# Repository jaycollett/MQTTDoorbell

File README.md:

# MQTTDoorbell

This repo contains all the project artifacts for my MQTT "smartifier" doorbell module. The module detects a push of the wired doorbell button and triggers a relay to ring the doorbell, the ESP8266 detects this as well and sends a MQTT message to let my HASS.IO server know. From there I trigger automated notifications as well as playing a doorbell MP3 on my Sonos speakers throughout my home.

Please visit my write-up of [this project to get more details](https://www.jaycollett.com/2019/03/a-smarter-doorbell-without-all-the-extras/).

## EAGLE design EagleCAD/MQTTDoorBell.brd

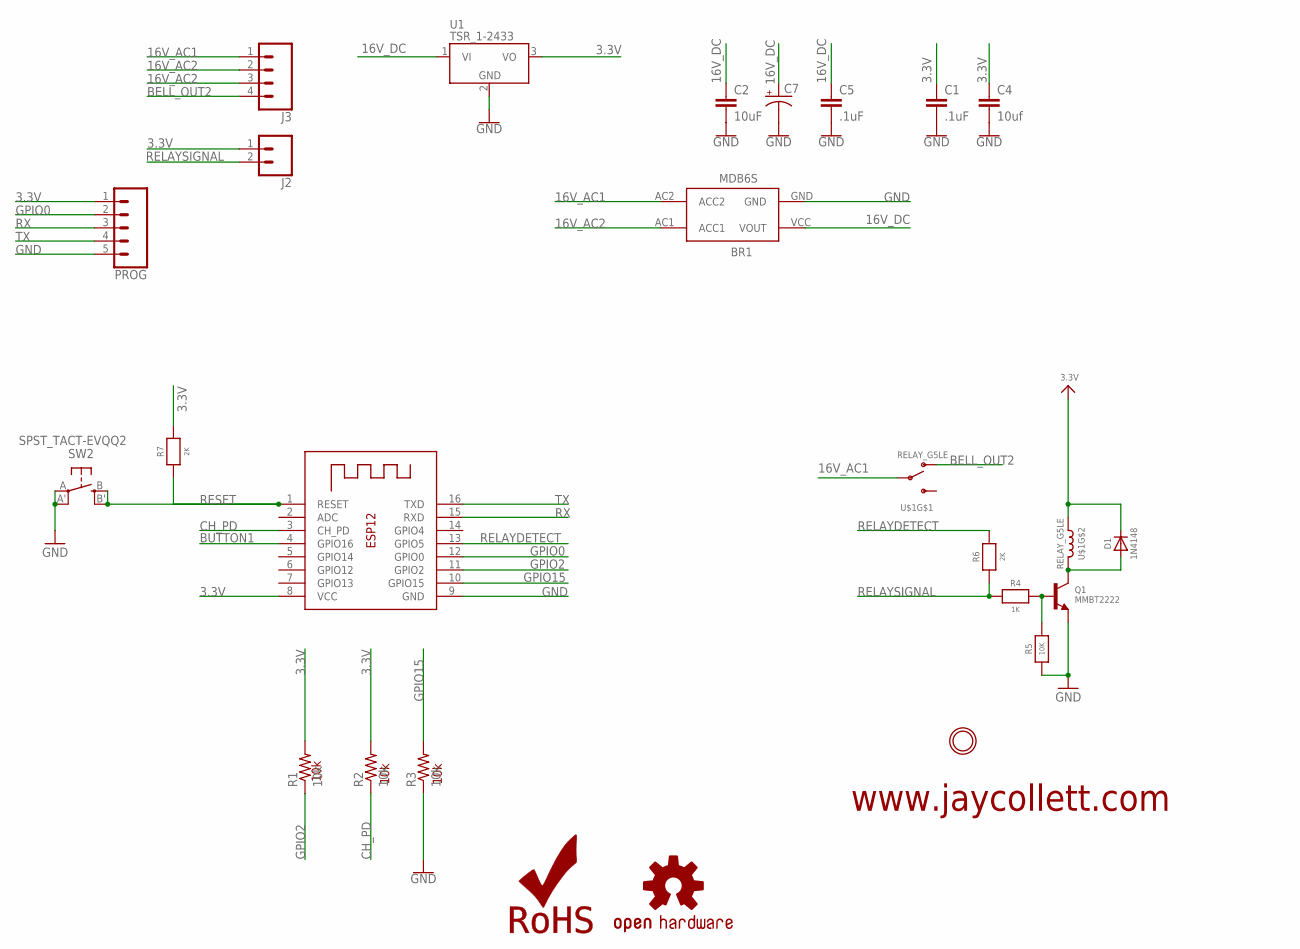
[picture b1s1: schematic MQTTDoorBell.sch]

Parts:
BR1: MDB6S; MICRO-DIP
C1, C5: .1uF; 0805
C2: 10uF; 0805
C4: 10uf; 0805
C7: CPOL-USE5-10.5; E5-10,5
D1: 1N4148; SOD-323
J2: CONN_023.5MM; SCREWTERMINAL-3.5MM-2
J3: CONN_04SCREW; SCREWTERMINAL-3.5MM-4
LOGO1: OSHW-LOGOMINI; OSHW-LOGO-MINI
LOGO2: ROHS_LOGO; ROHS_LOGO_0.18_IN
PROG: CONN_05; 1X05
Q1: MMBT2222; SOT23-R
R1, R2, R3: 10k; M0805
R4: 1K; 0805-NO
R5: 10K; 0805-NO
R6, R7: 2K; 0805-NO
SW2: SPST_TACT-EVQQ2; EVQ-Q2
U1: TSR_1-2433; TSR-1
U$1: RELAY_G5LE; RELAY_G5LE-1
U$4: MICROBUILDER_MOUNTINGHOLE3.0THIN; MICROBUILDER_MOUNTINGHOLE_3.0_PLATEDTHIN
X1: ESP-12

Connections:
3.3V: C1.1, C4.1, D1.C, J2.1, PROG.1, R1.2, R2.2, R7.2, U1.3 (VO), U$1.2 (1), X1.8 (VCC)
16V_AC1: BR1.AC2 (ACC2), J3.1, U$1.1
16V_AC2: BR1.AC1 (ACC1), J3.2, J3.3
16V_DC: BR1.VCC (VOUT), C2.1, C5.1, C7.+, U1.1 (VI)
BELL_OUT2: J3.4, U$1.3 (O)
BUTTON1: X1.4 (GPIO16)
CH_PD: R2.1, X1.3 (CH_PD)
GND: BR1.GND, C1.2, C2.2, C4.2, C5.2, C7.-, PROG.5, Q1.2 (E), R3.1, R5.1, SW2.A, SW2.A' (P1), U1.2 (GND), X1.9 (GND)
GPIO0: PROG.2, X1.12 (GPIO0)
GPIO2: R1.1, X1.11 (GPIO2)
GPIO15: R3.2, X1.10 (GPIO15)
unnamed: D1.A, Q1.3 (C), U$1.5 (2)
unnamed: Q1.1 (B), R4.2, R5.2
RELAYDETECT: R6.2, X1.13 (GPIO5)
RELAYSIGNAL: J2.2, R4.1, R6.1
RESET: R7.1, SW2.B (S), SW2.B' (S1), X1.1 (RESET)
RX: PROG.3, X1.15 (RXD)
TX: PROG.4, X1.16 (TXD)

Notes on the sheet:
10k
www.jaycollett.com

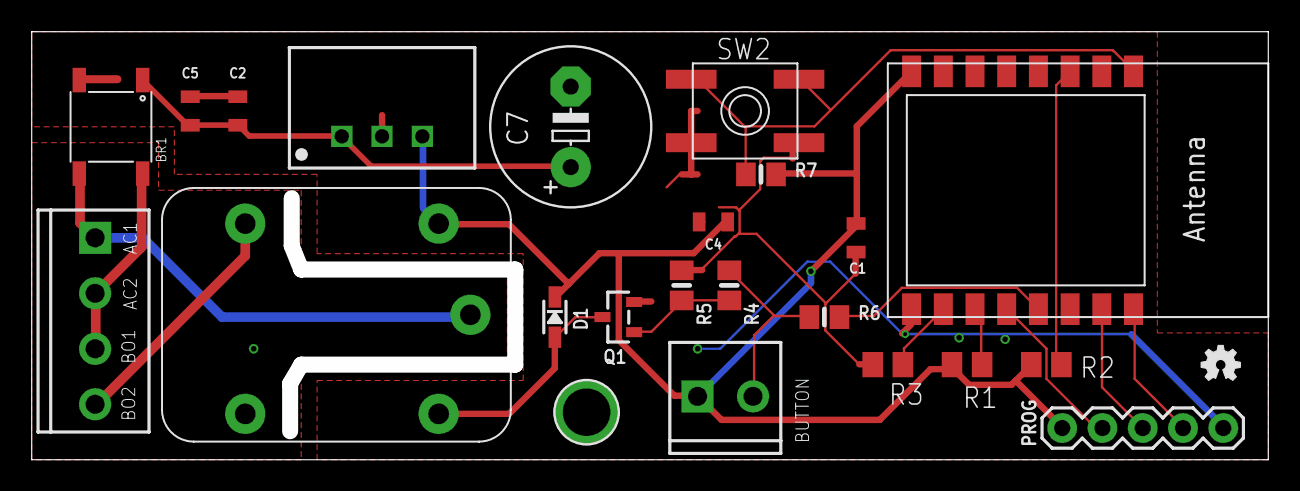
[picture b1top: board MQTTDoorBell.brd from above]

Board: 2 copper layers, 77.0 x 26.0 mm, 25 parts (1 on the bottom side), 17 nets.

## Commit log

2019-01-09 finish power rectifier and filtering
2019-01-09 fix folder structure of project
2019-01-11 updating design and starting to structure board
2019-01-21 initial commit of eagle files, version 1 of board'
2019-01-22 fix polygon issue and add labels'
2019-02-04 add new PCB board and schematic, add first draf of firmware
2019-02-04 add wifi reconnect routines
2019-02-04 updated issue with detecting doorbell pushes, validated mqtt topic and functionality.
2019-02-04 add power supply ripple measurement
2019-02-17 added first draft of enclosure
2019-02-17 fixing enclosure based on first print issues...
2019-02-17 added reset button shaft, tweak screw hole position
2019-02-17 tweaking position of bottom screw hole to align better
2019-02-17 tweaked lenght of reset shaft and position of female screw socket
2019-02-18 adding enclosure images
2019-02-18 fixing critical error with AC power lines to doorbell ringer
2021-01-09 rename arduino folder and add travis ci support

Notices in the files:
parts and their libraries:
SparkFun-Connectors: Licensing: Creative Commons ShareAlike 4.0 International - https://creativecommons.org/licenses/by-sa/4.0
microbuilder: This work is placed in the public domain, and may be freely used for commercial and non-commercial work with the following conditions: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
